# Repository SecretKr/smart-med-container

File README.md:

# Smart Medecine Container

Notify when it's time for medicine.

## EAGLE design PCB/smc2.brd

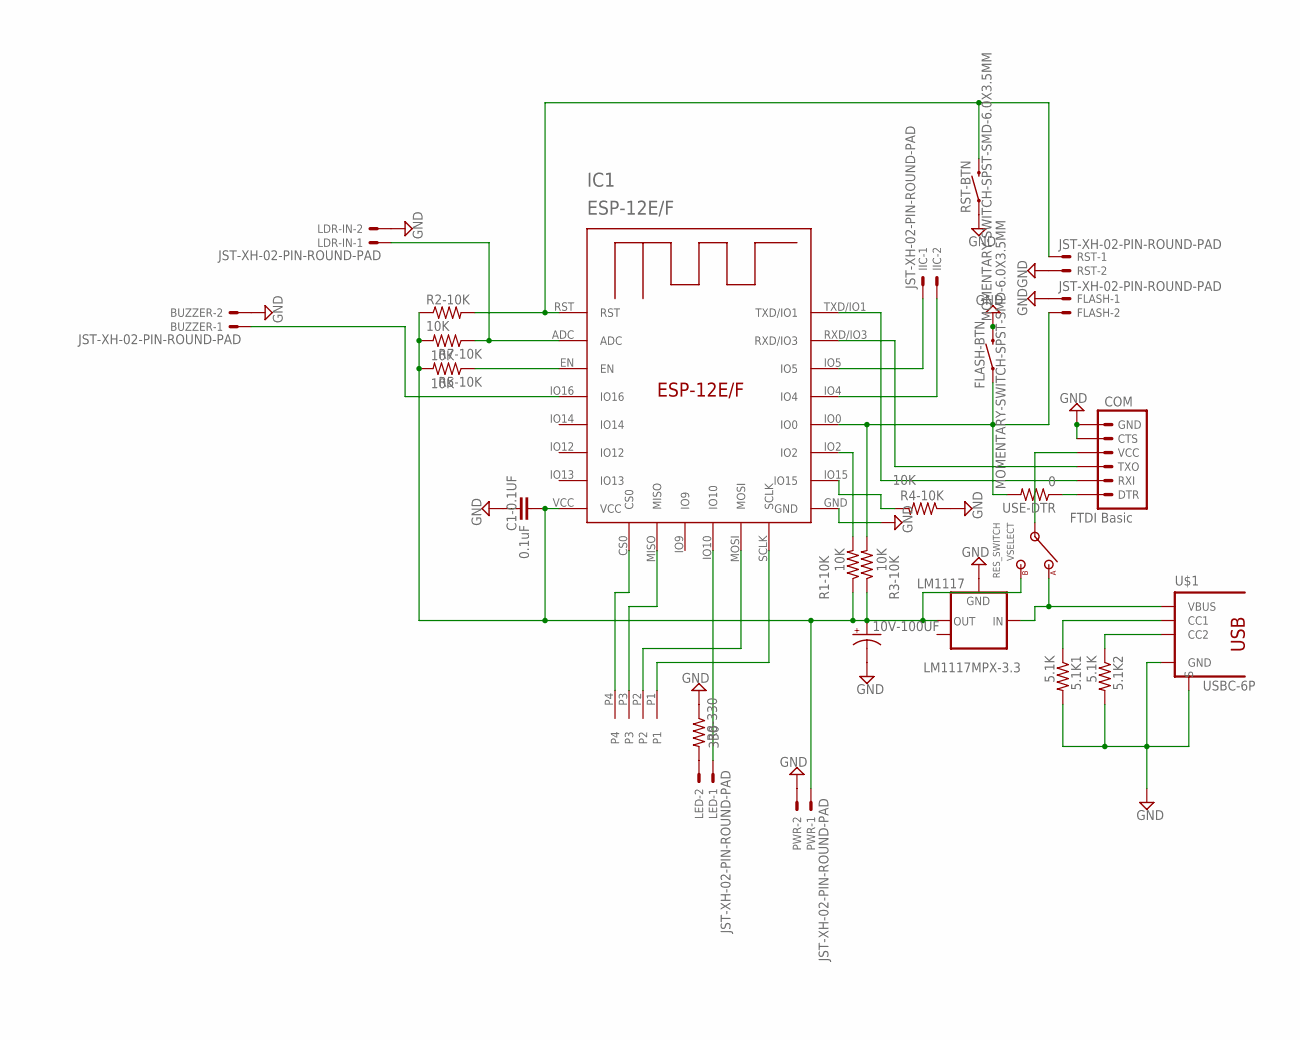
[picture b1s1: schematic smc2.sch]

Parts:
5.1K1, 5.1K2: 5.1K; 0603-RES
10V-100UF: CPOL-USA/3216-18W; A/3216-18W
BUZZER: JST-XH-02-PIN-ROUND-PAD; JST-XH-02-PACKAGE-ROUND-PAD
C1-0.1UF: 0.1uF; 0603-CAP
COM: FTDI Basic; 1X06
FLASH: JST-XH-02-PIN-ROUND-PAD; JST-XH-02-PACKAGE-ROUND-PAD
FLASH-BTN: MOMENTARY-SWITCH-SPST-SMD-6.0X3.5MM; TACTILE_SWITCH_SMD_6.0X3.5MM
IC1: ESP-12E/F; ESP-12E
IIC: JST-XH-02-PIN-ROUND-PAD; JST-XH-02-PACKAGE-ROUND-PAD
LDR-IN: JST-XH-02-PIN-ROUND-PAD; JST-XH-02-PACKAGE-ROUND-PAD
LED: JST-XH-02-PIN-ROUND-PAD; JST-XH-02-PACKAGE-ROUND-PAD
LM1117: LM1117MPX-3.3; SOT223
PWR: JST-XH-02-PIN-ROUND-PAD; JST-XH-02-PACKAGE-ROUND-PAD
R1-10K, R2-10K, R3-10K, R4-10K, R5-10K, R7-10K: 10K; 0603-RES
R8-330: 330; 0603-RES
RST: JST-XH-02-PIN-ROUND-PAD; JST-XH-02-PACKAGE-ROUND-PAD
RST-BTN: MOMENTARY-SWITCH-SPST-SMD-6.0X3.5MM; TACTILE_SWITCH_SMD_6.0X3.5MM
U$1: USBC-6P; USCX-06FX-XXMX-01
U$3: 4PIN
USE-DTR: 0; 0603-RES
VSELECT: RES_SWITCH

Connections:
3V3: 10V-100UF.+, C1-0.1UF.1, IC1.VCC, LM1117.2 (OUT), PWR.1, R1-10K.1, R2-10K.1, R3-10K.1, R5-10K.2, R7-10K.2, VSELECT.B
5V: LM1117.3 (IN), U$1.VBUS1 (VBUS), U$1.VBUS2 (VBUS), VSELECT.A
GND: 5.1K1.2, 5.1K2.2, 10V-100UF.-, BUZZER.2, C1-0.1UF.2, COM.5 (CTS), COM.6 (GND), FLASH.1, FLASH-BTN.2, IC1.GND, LDR-IN.2, LM1117.1 (GND), PWR.2, R4-10K.1, R8-330.1, RST.2, RST-BTN.1, U$1.GND1 (GND), U$1.GND2 (GND), U$1.SHIELD1 (S), U$1.SHIELD2 (S), U$1.SHIELD3 (S), U$1.SHIELD4 (S)
IO0: FLASH.2, FLASH-BTN.1, IC1.IO0, R3-10K.2, USE-DTR.2
IO2: IC1.IO2, R1-10K.2
IO10: IC1.IO10, LED.1
unnamed: IC1.IO15, R4-10K.2
unnamed: IC1.EN, R5-10K.1
unnamed: IC1.SCLK, U$3.P1
unnamed: COM.4 (VCC), VSELECT.C (IN)
unnamed: LED.2, R8-330.2
unnamed: COM.3 (TXO), IC1.RXD/IO3
unnamed: COM.2 (RXI), IC1.TXD/IO1
unnamed: COM.1 (DTR), USE-DTR.1
unnamed: IC1.MOSI, U$3.P2
unnamed: IC1.MISO, U$3.P3
unnamed: 5.1K2.1, U$1.CC2
unnamed: 5.1K1.1, U$1.CC1
unnamed: BUZZER.1, IC1.IO16
unnamed: IC1.IO5, IIC.1
unnamed: IC1.IO4, IIC.2
unnamed: IC1.ADC, LDR-IN.1, R7-10K.1
unnamed: IC1.CS0, U$3.P4
RST: IC1.RST, R2-10K.2, RST.1, RST-BTN.2

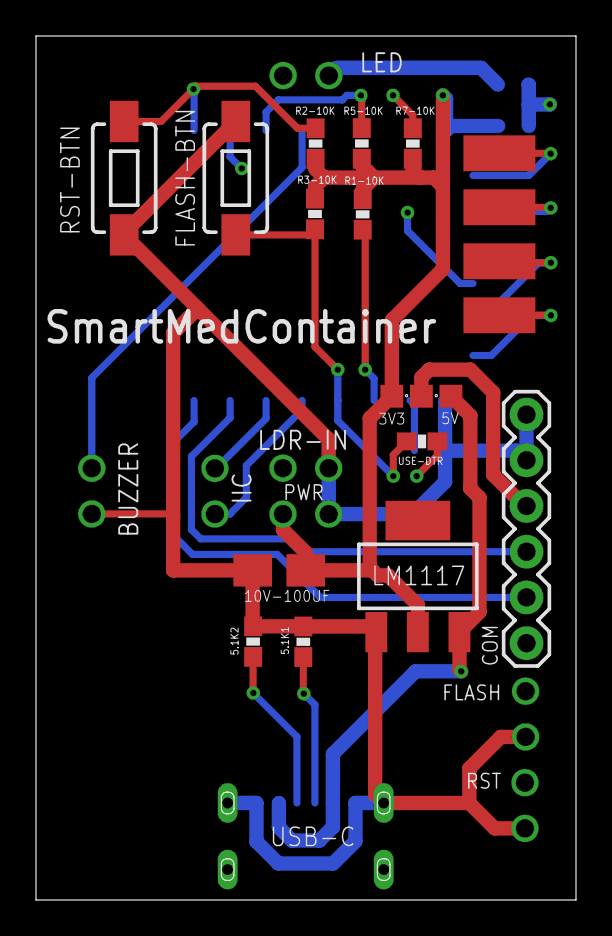
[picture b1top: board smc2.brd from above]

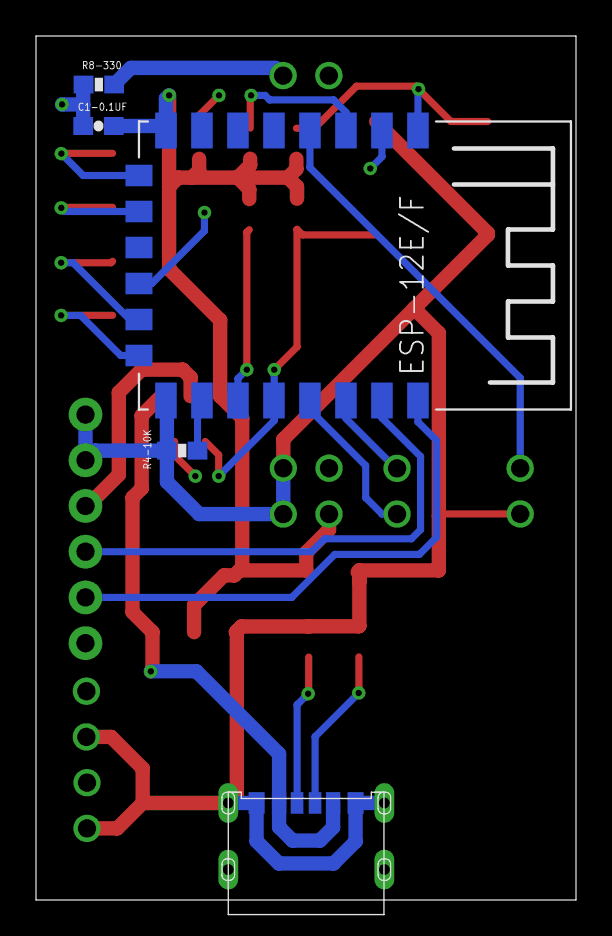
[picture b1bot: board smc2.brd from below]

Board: 4 copper layers, 30.0 x 48.0 mm, 27 parts (5 on the bottom side), 24 nets.

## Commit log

2021-12-08 ESP12
2021-12-22 add logo
2021-12-22 ios app
2021-12-27 add led, web
2021-12-29 ios app (not finished)
2022-01-02 fix Readme
2022-01-04 PCB v2
2022-01-05 3d model
2022-01-05 new status page
2022-01-05 Update code
2022-01-05 Update ignore gcode
2022-01-05 Testing code
2022-01-11 update 3d
2022-01-11 sensor test
2022-01-11 secret
2022-01-11 arduino secret
2022-01-11 update gitignore
2023-05-03 add page

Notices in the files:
parts and their libraries:
SparkFun-Switches: Licensing: Creative Commons ShareAlike 4.0 International - https://creativecommons.org/licenses/by-sa/4.0
